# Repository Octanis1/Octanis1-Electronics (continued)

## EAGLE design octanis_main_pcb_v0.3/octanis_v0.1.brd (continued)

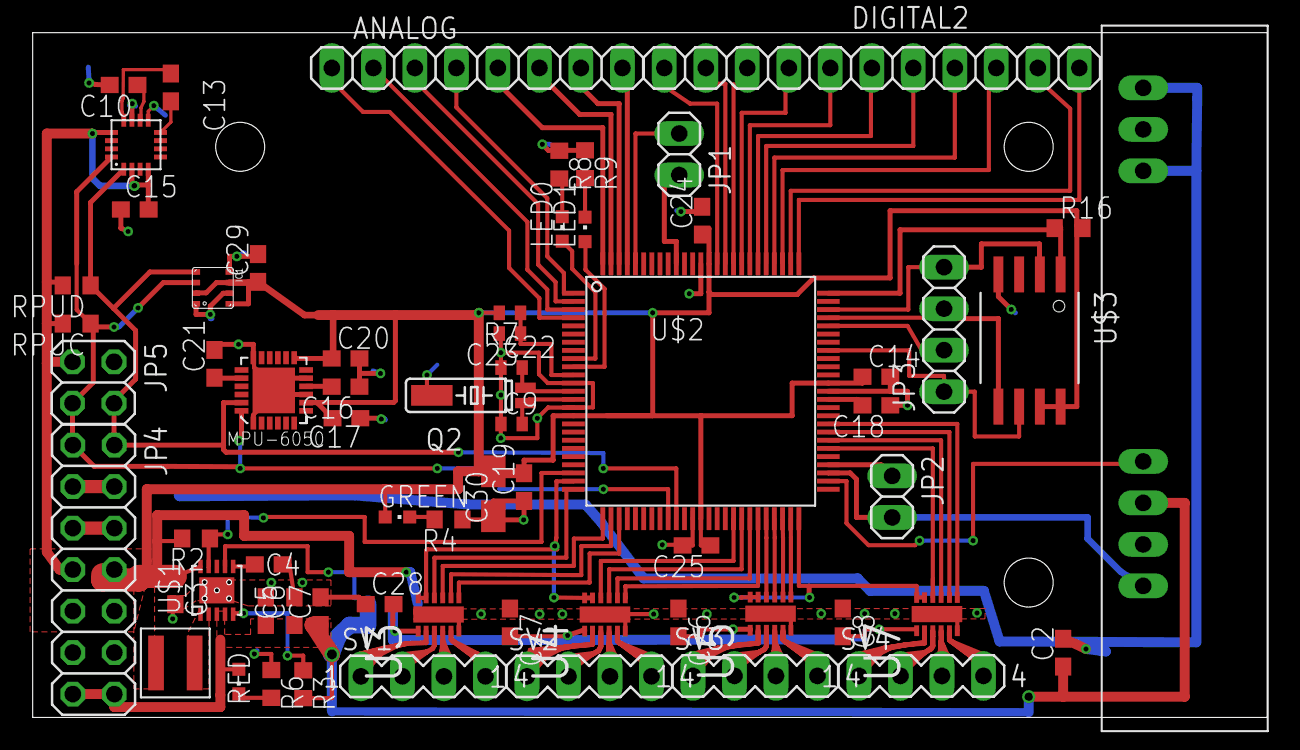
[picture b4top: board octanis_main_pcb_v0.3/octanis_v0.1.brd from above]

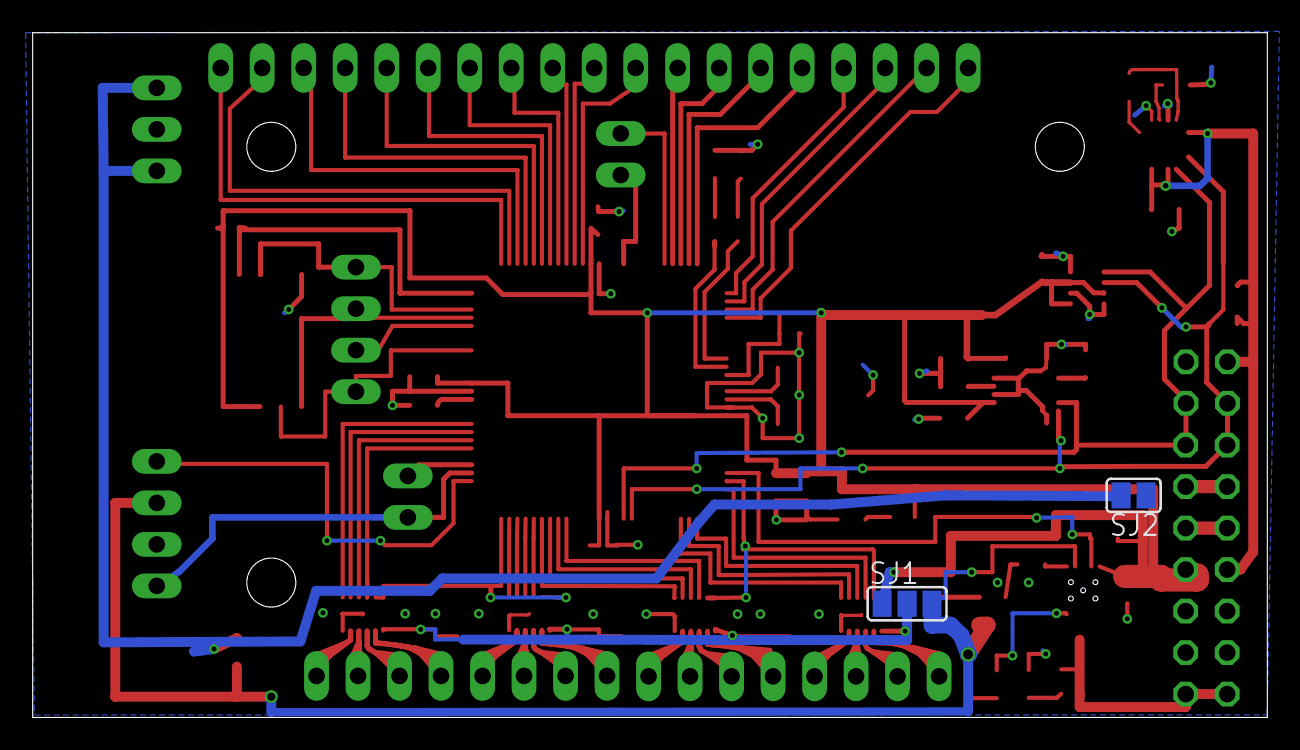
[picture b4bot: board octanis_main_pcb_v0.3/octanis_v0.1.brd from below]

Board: 2 copper layers, 75.6 x 41.9 mm, 67 parts (2 on the bottom side), 89 nets.

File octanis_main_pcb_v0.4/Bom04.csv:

"Qty";"Value";"Device";"Package";"Parts";"Description";"MF";"MPN";"OC_FARNELL";"OC_NEWARK";"PACKAGE";"SUPPLIER";
"4";"";"MA04-1";"MA04-1";"SV1, SV2, SV3, SV4";"PIN HEADER";"";"";"unknown";"unknown";"";"";
"1";"";"PINHD-1X72MM";"1:07X2MM";"JP1";"PIN HEADER";"";"";"";"";"";"";
"1";"";"PINHD-2X2";"2X02";"JP5";"PIN HEADER";"";"";"";"";"";"";
"1";"";"PINHD-2X7";"2X07";"JP4";"PIN HEADER";"";"";"";"";"";"";
"1";"";"SJ";"SJ";"SJ2";"SMD solder JUMPER";"";"";"";"";"";"";
"1";"0R";"R-EU_R0402";"R0402";"R7";"RESISTOR, European symbol";"";"";"";"";"";"";
"2";"100n";"C-EUC0402";"C0402";"C1, C23";"CAPACITOR, European symbol";"";"";"";"";"";"";
"8";"100n";"C-EUC0603";"C0603";"C2, C11, C15, C16, C18, C19, C20, C29";"CAPACITOR, European symbol";"";"";"";"";"";"";
"3";"10k";"R-EU_R0603";"R0603";"R16, RPUC, RPUD";"RESISTOR, European symbol";"";"";"";"";"";"";
"1";"10n";"C-EUC0603";"C0603";"C17";"CAPACITOR, European symbol";"";"";"";"";"";"";
"1";"10nF";"C-EUC0603";"C0603";"C4";"CAPACITOR, European symbol";"";"";"";"";"";"";
"2";"10u";"CPOL-EUA/3216-18R";"A/3216-18R";"C25, C30";"POLARIZED CAPACITOR, European symbol";"";"";"";"";"";"";
"2";"12p";"C-EUC0402";"C0402";"C9, C22";"CAPACITOR, European symbol";"";"";"";"";"";"";
"2";"1M";"R-EU_R0603";"R0603";"R2, R3";"RESISTOR, European symbol";"";"";"";"";"";"";
"4";"1k";"R-EU_R0603";"R0603";"R4, R6, R8, R9";"RESISTOR, European symbol";"";"";"";"";"";"";
"1";"1uH";"XFL4020";"XFL4020";"L1";"";"";"";"";"";"";"";
"1";"2.2n";"C-EUC0603";"C0603";"C21";"CAPACITOR, European symbol";"";"";"";"";"";"";
"1";"220n";"C-EUC0603";"C0603";"C13";"CAPACITOR, European symbol";"";"";"";"";"";"";
"3";"22uF";"C-EUC0603";"C0603";"C3, C5, C6";"CAPACITOR, European symbol";"";"";"";"";"";"";
"1";"3 x 22uF";"C-EUC0603";"C0603";"C7";"CAPACITOR, European symbol";"";"";"";"";"";"";
"1";"32.768kHz";"MS3V-T1R";"MS3V-T1R";"Q2";"";"";"";"";"";"";"";
"1";"3V-ok";"LEDCHIPLED_0603";"CHIPLED_0603";"GREEN";"LED";"";"";"";"";"";"";
"1";"3V3  V_Motor  5V";"SJ2W";"SJ_2";"SJ1";"SMD solder JUMPER";"";"";"";"";"";"";
"1";"4.7u";"C-EUC0603";"C0603";"C10";"CAPACITOR, European symbol";"";"";"";"";"";"";
"1";"4.7uH";"LQM2MP_G0";"0806";"L3";"";"";"";"";"";"";"";
"4";"470n";"C-EUC0603";"C0603";"C8, C26, C27, C28";"CAPACITOR, European symbol";"";"";"";"";"";"";
"1";"5V-ok";"LEDCHIPLED_0603";"CHIPLED_0603";"RED";"LED";"";"";"";"";"";"";
"1";"91k 0.1% ±25 ppm/°C";"R-EU_R0402";"R0402";"R10";"RESISTOR, European symbol";"";"";"";"";"";"";
"1";"A18:A8";"PINHD-1X11";"1X11";"GPIO2";"PIN HEADER";"";"";"";"";"";"";
"1";"A7:A0";"PINHD-1X8";"1X08";"GPIO1";"PIN HEADER";"";"";"";"";"";"";
"1";"BME280";"BME280";"BME280";"IC1";"DIGITAL HUMIDITY, PRESSURE AND TEMPERATURE SENSOR* Digital interface I²C (up to 3.4 MHz) and SPI (3 and 4 wire, up to 10 MHz)* Supply voltage VDD main supply voltage range: 1.71 V to 3.6 V*VDDIO interface voltage range: 1.2 V to 3.6 V";"";"";"";"";"";"";
"4";"DRV8836DSSR";"DRV8836DSSR";"SON50P200X300X80-13N";"U3, U4, U5, U7";"DUAL LOW VOLTAGE H-BRIDGE IC,SON-12";"";"DRV8836DSSR ";"2115236 ";"94T6066";"SON-12";"TEXAS INSTRUMENTS";
"1";"HMC5883L ";"HMC5883L";"LPCC16";"COMPASS";"";"";"";"";"";"";"";
"1";"HX1";"HX1";"HX1";"U$4";"Radiometrix HX1:";"";"";"";"";"";"";
"1";"LED0";"LEDCHIPLED_0603";"CHIPLED_0603";"LED0";"LED";"";"";"";"";"";"";
"1";"LED1";"LEDCHIPLED_0603";"CHIPLED_0603";"LED1";"LED";"";"";"";"";"";"";
"1";"MPU-6050";"MPU-6050";"QFN24";"MPU-6050";"";"";"";"";"";"";"";
"1";"MSP432";"MSP432";"PZ100";"MSP1";"";"";"";"";"";"";"";
"1";"SPI";"PINHD-1X4";"1X04";"JP3";"PIN HEADER";"";"";"";"";"";"";
"1";"SST25VF064C";"SST25VF064C";"SOIC_8-LEAD";"U$3";"";"";"";"";"";"";"";
"1";"STARGND";"STARGND";"STAR";"U$2";"";"";"";"";"";"";"";
"1";"TPS61232";"TPS61232";"S-PVSON-N10";"U$1";"Up to 96% Efficiency Synchronous Boost Converter";"";"";"";"";"";"";
